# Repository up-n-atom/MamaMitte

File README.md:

# MamaMitte Reproduction

## Schematic Capture

- [x] Create symbols
- [ ] Block design
  - [x] Memory
  - [x] RTC
  - [ ] Infrared *(Hi-res image pending)*

## PCB Layout

- [x] Create footprints
- [ ] Route top layer 
- [x] Route bottom layer
- [ ] Plane top layer
- [x] Plane bottom layer
- [ ] Teardrop top layer
- [ ] Teardrop bottom layer

## WIP

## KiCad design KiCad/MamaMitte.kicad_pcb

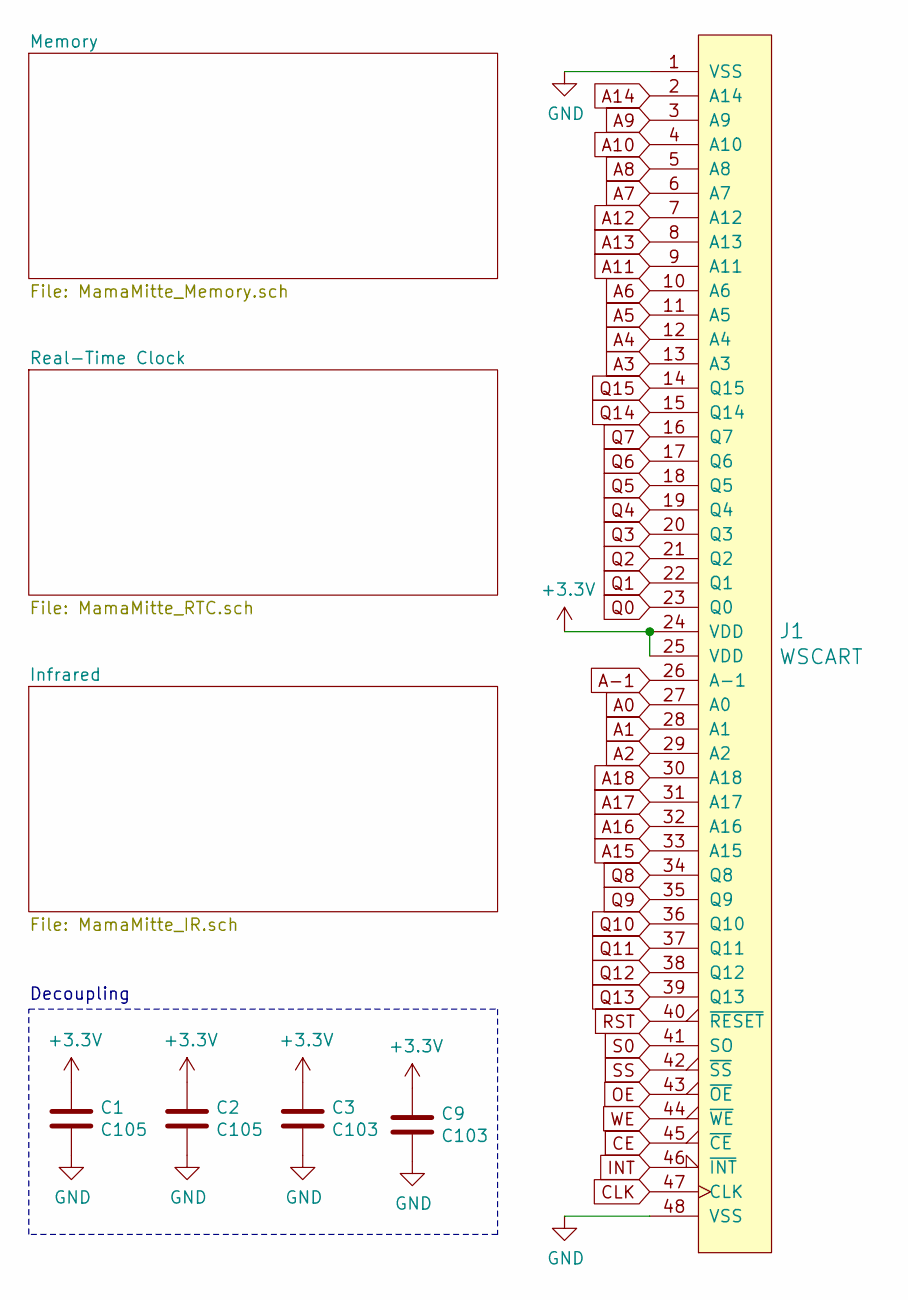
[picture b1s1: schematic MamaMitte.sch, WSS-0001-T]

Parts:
C1, C2: C105; C_0402_1005Metric
C3, C9: C103; C_0402_1005Metric
J1: WSCART; WSCE-48_P1.25mm

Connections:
+3V3: C1.1, C2.1, C3.1, C9.1, J1.24 (VDD), J1.25 (VDD); also elsewhere on the board
A0: J1.27 (A0); also elsewhere on the board
A1: J1.28 (A1); also elsewhere on the board
A2: J1.29 (A2); also elsewhere on the board
A3: J1.13 (A3); also elsewhere on the board
A4: J1.12 (A4); also elsewhere on the board
A5: J1.11 (A5); also elsewhere on the board
A6: J1.10 (A6); also elsewhere on the board
A7: J1.6 (A7); also elsewhere on the board
A8: J1.5 (A8); also elsewhere on the board
A9: J1.3 (A9); also elsewhere on the board
A10: J1.4 (A10); also elsewhere on the board
A11: J1.9 (A11); also elsewhere on the board
A12: J1.7 (A12); also elsewhere on the board
A13: J1.8 (A13); also elsewhere on the board
A14: J1.2 (A14); also elsewhere on the board
A15: J1.33 (A15); also elsewhere on the board
A16: J1.32 (A16); also elsewhere on the board
A17: J1.31 (A17); also elsewhere on the board
A18: J1.30 (A18); also elsewhere on the board
A-1: J1.26 (A-1); also elsewhere on the board
CE: J1.45 (~CE); also elsewhere on the board
CLK: J1.47 (CLK); also elsewhere on the board
GND: C1.2, C2.2, C3.2, C9.2, J1.1 (VSS), J1.48 (VSS); also elsewhere on the board
INT: J1.46 (~INT); also elsewhere on the board
OE: J1.43 (~OE); also elsewhere on the board
Q0: J1.23 (Q0); also elsewhere on the board
Q1: J1.22 (Q1); also elsewhere on the board
Q2: J1.21 (Q2); also elsewhere on the board
Q3: J1.20 (Q3); also elsewhere on the board
Q4: J1.19 (Q4); also elsewhere on the board
Q5: J1.18 (Q5); also elsewhere on the board
Q6: J1.17 (Q6); also elsewhere on the board
Q7: J1.16 (Q7); also elsewhere on the board
Q8: J1.34 (Q8); also elsewhere on the board
Q9: J1.35 (Q9); also elsewhere on the board
Q10: J1.36 (Q10); also elsewhere on the board
Q11: J1.37 (Q11); also elsewhere on the board
Q12: J1.38 (Q12); also elsewhere on the board
Q13: J1.39 (Q13); also elsewhere on the board
Q14: J1.15 (Q14); also elsewhere on the board
Q15: J1.14 (Q15); also elsewhere on the board
RST: J1.40 (~RESET); also elsewhere on the board
S0: J1.41 (SO)
SS: J1.42 (~SS); also elsewhere on the board
WE: J1.44 (~WE); also elsewhere on the board

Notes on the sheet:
Decoupling

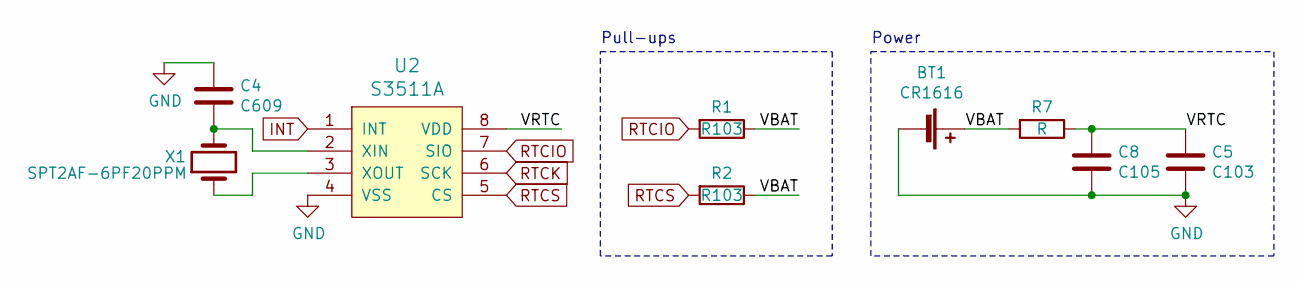
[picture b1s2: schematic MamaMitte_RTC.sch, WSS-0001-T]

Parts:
BT1: CR1616; BatteryHolder_3N1_CR1616
C4: C609; C_0402_1005Metric
C5: C103; C_0402_1005Metric
C8: C105; C_0402_1005Metric
R1, R2: R103; R_0402_1005Metric
R7: R; R_0402_1005Metric
U2: S3511A; SSOP-8_4.4x3mm_P0.65mm
X1: SPT2AF-6PF20PPM; Oscillator_SMD_SeikoEpson_SPT2AF-4Pin_8.7x3.7mm

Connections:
/Real-Time Clock/VBAT: BT1.1 (+), R1.1, R2.1, R7.2
/Real-Time Clock/VRTC: C5.1, C8.1, R7.1, U2.8 (VDD)
GND: BT1.2 (-), C4.1, C5.2, C8.2, U2.4 (VSS); also elsewhere on the board
INT: U2.1 (INT); also elsewhere on the board
unnamed: C4.2, U2.2 (XIN), X1.4
unnamed: U2.3 (XOUT), X1.1
RTCIO: R1.2, U2.7 (SIO); also elsewhere on the board
RTCK: U2.6 (SCK); also elsewhere on the board
RTCS: R2.2, U2.5 (CS); also elsewhere on the board

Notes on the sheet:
Pull-ups
Power

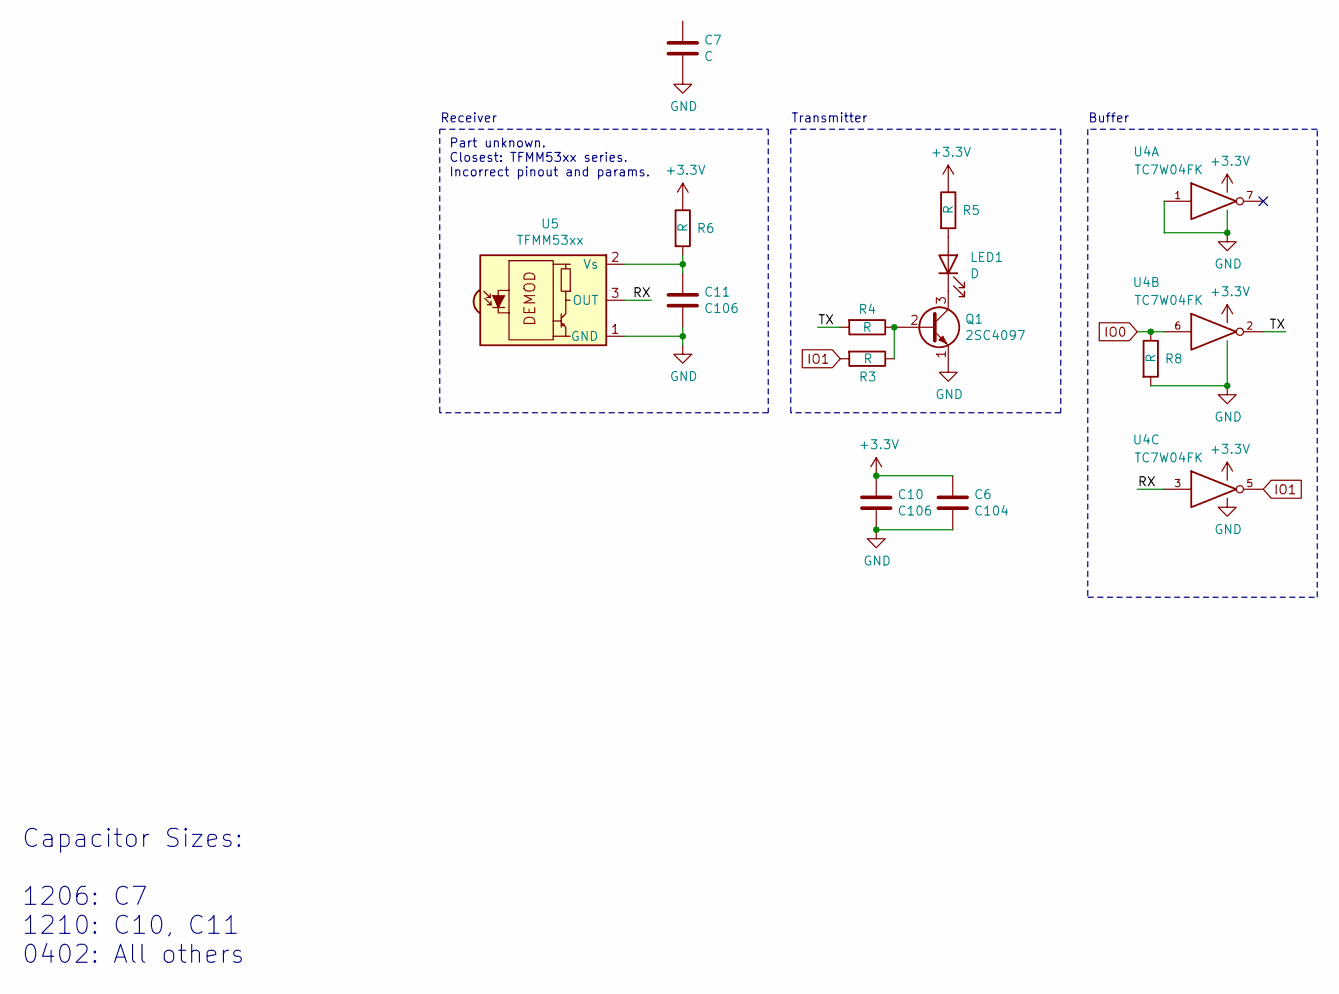
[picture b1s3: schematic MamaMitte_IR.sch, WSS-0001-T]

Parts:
C6: C104; C_0402_1005Metric
C7: C; C_1206_3216Metric
C10, C11: C106; C_1210_3225Metric
LED1: D; LED_1206_3216Metric
Q1: 2SC4097; SOT-323_SC-70
R3, R4, R5, R6, R8: R; R_0402_1005Metric
U4: TC7W04FK; SSOP-8_2.3x2mm_P0.5mm
U5: TFMM53xx; Vishay_TFMM5xx0

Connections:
+3V3: C6.1, C10.1, R5.1, R6.1, U4.8 (VCC); also elsewhere on the board
/Infrared/RX: U4.3, U5.3 (OUT)
/Infrared/TX: R4.2, U4.2
GND: C6.2, C7.2, C10.2, C11.2, Q1.1 (E), R8.2, U4.1, U4.4 (GND), U5.1 (GND); also elsewhere on the board
IO0: R8.1, U4.6; also elsewhere on the board
IO1: R3.2, U4.5; also elsewhere on the board
unnamed: C11.1, R6.2, U5.2 (Vs)
unnamed: LED1.1 (K), Q1.3 (C)
unnamed: LED1.2 (A), R5.2
unnamed: Q1.2 (B), R3.1, R4.1

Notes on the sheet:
Buffer
Transmitter
Receiver
Part unknown. Closest: TFMM53xx series. Incorrect pinout and params.
Capacitor Sizes: 1206: C7 1210: C10, C11 0402: All others

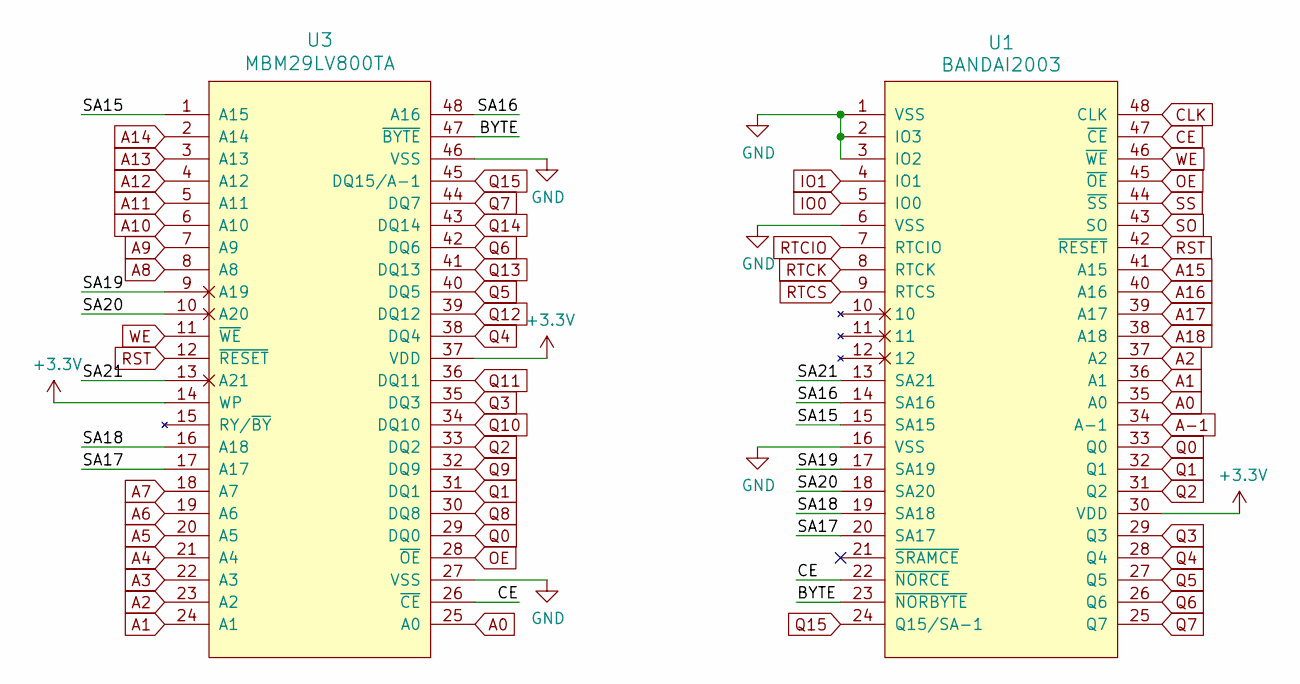
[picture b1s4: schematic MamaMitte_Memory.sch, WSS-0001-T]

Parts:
U1: BANDAI2003; LQFP-48_7x7mm_P0.5mm
U3: MBM29LV800TA; TSOP-I-48_18.4x12mm_P0.5mm

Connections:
+3V3: U1.30 (VDD), U3.14 (WP), U3.37 (VDD); also elsewhere on the board
/Memory/BYTE: U1.23 (~NORBYTE), U3.47 (~BYTE)
/Memory/SA15: U1.15 (SA15), U3.1 (A15)
/Memory/SA16: U1.14 (SA16), U3.48 (A16)
/Memory/SA17: U1.20 (SA17), U3.17 (A17)
/Memory/SA18: U1.19 (SA18), U3.16 (A18)
/Memory/SA19: U1.17 (SA19), U3.9 (A19)
/Memory/SA20: U1.18 (SA20), U3.10 (A20)
/Memory/SA21: U1.13 (SA21), U3.13 (A21)
A0: U1.35 (A0), U3.25 (A0); also elsewhere on the board
A1: U1.36 (A1), U3.24 (A1); also elsewhere on the board
A2: U1.37 (A2), U3.23 (A2); also elsewhere on the board
A3: U3.22 (A3); also elsewhere on the board
A4: U3.21 (A4); also elsewhere on the board
A5: U3.20 (A5); also elsewhere on the board
A6: U3.19 (A6); also elsewhere on the board
A7: U3.18 (A7); also elsewhere on the board
A8: U3.8 (A8); also elsewhere on the board
A9: U3.7 (A9); also elsewhere on the board
A10: U3.6 (A10); also elsewhere on the board
A11: U3.5 (A11); also elsewhere on the board
A12: U3.4 (A12); also elsewhere on the board
A13: U3.3 (A13); also elsewhere on the board
A14: U3.2 (A14); also elsewhere on the board
A15: U1.41 (A15); also elsewhere on the board
A16: U1.40 (A16); also elsewhere on the board
A17: U1.39 (A17); also elsewhere on the board
A18: U1.38 (A18); also elsewhere on the board
A-1: U1.34 (A-1); also elsewhere on the board
CE: U1.22 (~NORCE), U1.47 (~CE), U3.26 (~CE); also elsewhere on the board
CLK: U1.48 (CLK); also elsewhere on the board
GND: U1.1 (VSS), U1.2 (IO3), U1.3 (IO2), U1.6 (VSS), U1.16 (VSS), U3.27 (VSS), U3.46 (VSS); also elsewhere on the board
IO0: U1.5 (IO0); also elsewhere on the board
IO1: U1.4 (IO1); also elsewhere on the board
OE: U1.45 (~OE), U3.28 (~OE); also elsewhere on the board
Q0: U1.33 (Q0), U3.29 (DQ0); also elsewhere on the board
Q1: U1.32 (Q1), U3.31 (DQ1); also elsewhere on the board
Q2: U1.31 (Q2), U3.33 (DQ2); also elsewhere on the board
Q3: U1.29 (Q3), U3.35 (DQ3); also elsewhere on the board
Q4: U1.28 (Q4), U3.38 (DQ4); also elsewhere on the board
Q5: U1.27 (Q5), U3.40 (DQ5); also elsewhere on the board
Q6: U1.26 (Q6), U3.42 (DQ6); also elsewhere on the board
Q7: U1.25 (Q7), U3.44 (DQ7); also elsewhere on the board
Q8: U3.30 (DQ8); also elsewhere on the board
Q9: U3.32 (DQ9); also elsewhere on the board
Q10: U3.34 (DQ10); also elsewhere on the board
Q11: U3.36 (DQ11); also elsewhere on the board
Q12: U3.39 (DQ12); also elsewhere on the board
Q13: U3.41 (DQ13); also elsewhere on the board
Q14: U3.43 (DQ14); also elsewhere on the board
Q15: U1.24 (Q15/SA-1), U3.45 (DQ15/A-1); also elsewhere on the board
RST: U1.42 (~RESET), U3.12 (~RESET); also elsewhere on the board
RTCIO: U1.7 (RTCIO); also elsewhere on the board
RTCK: U1.8 (RTCK); also elsewhere on the board
RTCS: U1.9 (RTCS); also elsewhere on the board
SO: U1.43 (SO)
SS: U1.44 (~SS); also elsewhere on the board
WE: U1.46 (~WE), U3.11 (~WE); also elsewhere on the board

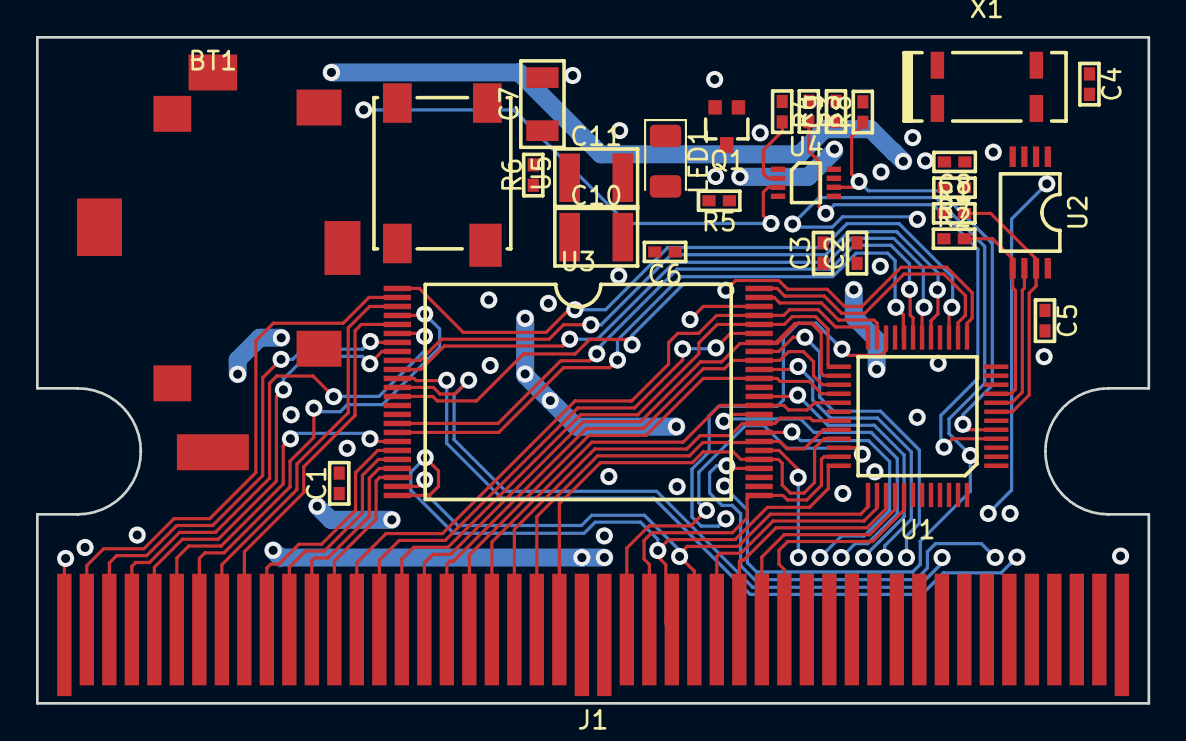
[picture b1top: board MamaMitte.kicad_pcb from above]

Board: 2 copper layers, 61.8 x 37.0 mm, 29 parts (0 on the bottom side), 68 nets.

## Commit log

2021-04-18 Add KiCad project
2021-04-18 Add datasheets
2021-04-18 Add images
    Images by ototo and pulled from https://blog-imgs-131-origin.fc2.com/o/t/o/ototo2009/WS-2019-12b.html
2021-04-18 Add image README
2021-04-19 Add board outline and vias
2021-04-19 Add RTC datasheet
2021-04-19 Add SPT2AF-6PF20PPM symbol
2021-04-19 Update RTC schematic
    Add crystal
2021-04-21 Add correct transistor datasheet
    Size: SOT-323 and marking 'C' match.
2021-04-23 Add footprints and assign nets
    Assigned and placed footprints, and assigned nets to vias.
2021-04-23 Add 3D rendering.
2021-04-23 Revert "Add 3D rendering."
    This reverts commit f3bbc0c60c7aa6163a6a1774d4b5d6e4995860f9.
2021-04-23 Add 3D rendering
2021-04-23 Add render to README
2021-04-23 Add bottom traces and ground plane
2021-04-24 Resize vias
    Use the via net class size.
2021-04-25 Add SP-T2A-F 3D model
    Designed in FreeCAD and exported using KiCadStepUp.
2021-04-25 Assign SP-T2A-F 3D model to footprint
2021-04-25 Move rendered image
2021-04-26 Add TFM5xx0 3D model
2021-04-26 Update 3D render
2021-04-27 Update schematic
    Fix Bandai 2003 pinout and RTC power.
2021-04-27 Begin routing top
2021-04-30 Update schematic
    Change power source for RTC pull-ups, and restructure IR block.
2021-04-30 Update netlist
